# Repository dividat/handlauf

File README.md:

# Handlauf

**PCB Design, Firmware and Driver vor the Dividat Handlauf Extension**

## PCB Design

See the `Handlauf.sch` and `Handlauf.brd` EAGLE files. The CAM output for
production can be found in the `cam.zip` file.

## Firmware

The `Handlauf.ino` is the Arduino based firmware for the built-in Arduino.
Download the "capacitive sensor" and "ewma" library from the Arduino library
manager.

## Driver

The `*.go` files make up the Go based driver for the sensor. It can be built
using the standard Go mechanisms. A compiled version for macOS is available on
the release page: https://github.com/256dpi/handlauf/releases. 

The binary provides the following options:

```
Usage of ./handlauf:
  -addr string
        WebSocket server address (default "0.0.0.0:8080")
  -debug string
        Debug server address e.g. ":1234"
  -freq int
        Sample publish frequency (default 60)
  -min-range float
        The minimum range (default 1000)
  -threshold float
        The threshold for on/off values
```

The driver contains a Web based debug interface to inspect the sensor values.
If the driver is started with the `-debug :1234` flag, the interface is
available at `http://0.0.0.0:1234`.

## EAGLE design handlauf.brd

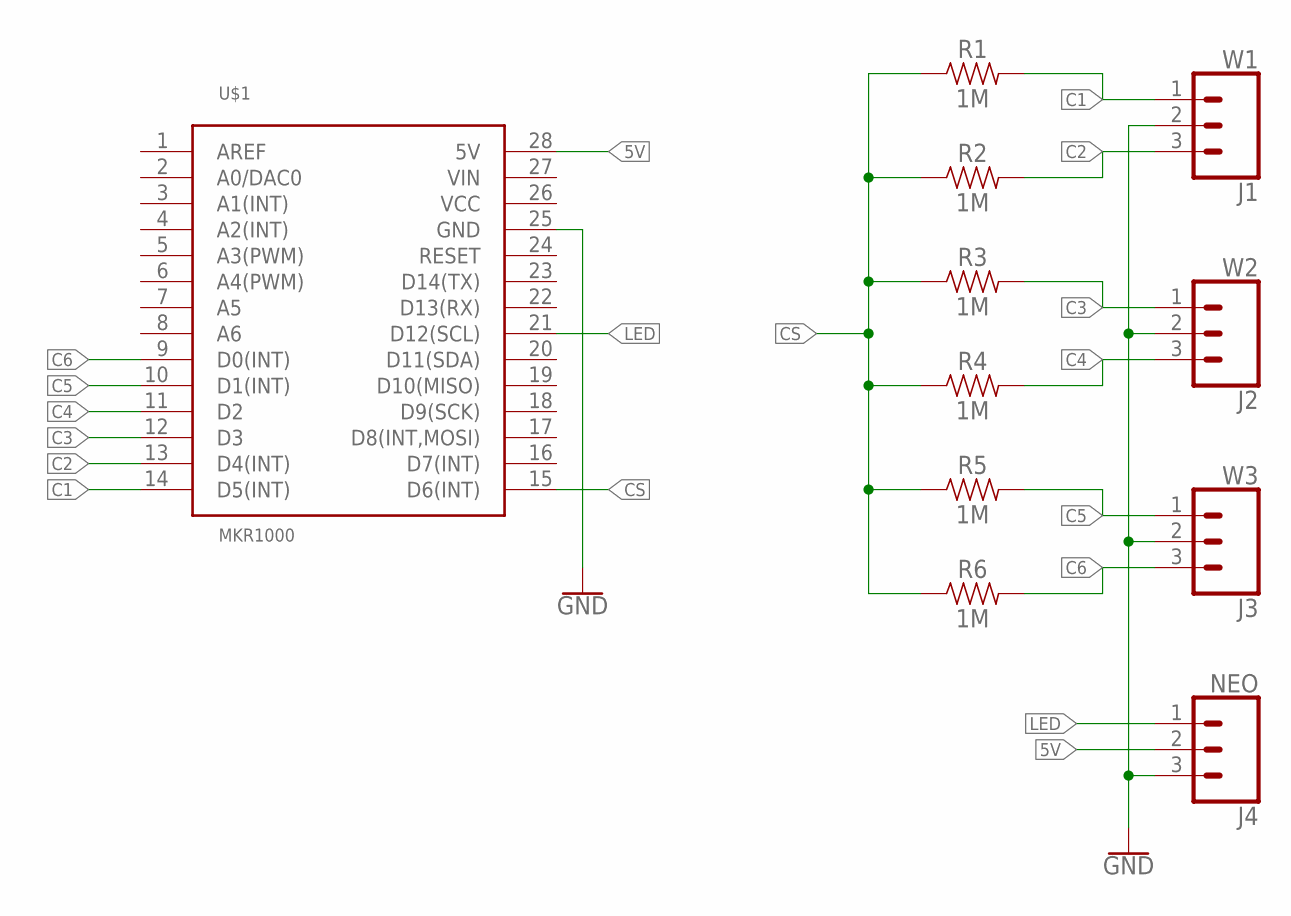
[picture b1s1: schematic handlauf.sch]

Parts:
J1: W1; SCREWTERMINAL-3.5MM-3
J2: W2; SCREWTERMINAL-3.5MM-3
J3: W3; SCREWTERMINAL-3.5MM-3
J4: NEO; 1X03
R1, R2, R3, R4, R5, R6: 1M; AXIAL-0.3
U$1: MKR1000; MKR1000-SOCKET

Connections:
5V: J4.2, U$1.28 (5V)
C1: J1.1, R1.P$2 (2), U$1.14 (D5(INT))
C2: J1.3, R2.P$2 (2), U$1.13 (D4(INT))
C3: J2.1, R3.P$2 (2), U$1.12 (D3)
C4: J2.3, R4.P$2 (2), U$1.11 (D2)
C5: J3.1, R5.P$2 (2), U$1.10 (D1(INT))
C6: J3.3, R6.P$2 (2), U$1.9 (D0(INT))
CS: R1.P$1 (1), R2.P$1 (1), R3.P$1 (1), R4.P$1 (1), R5.P$1 (1), R6.P$1 (1), U$1.15 (D6(INT))
GND: J1.2, J2.2, J3.2, J4.3, U$1.25 (GND)
LED: J4.1, U$1.21 (D12(SCL))

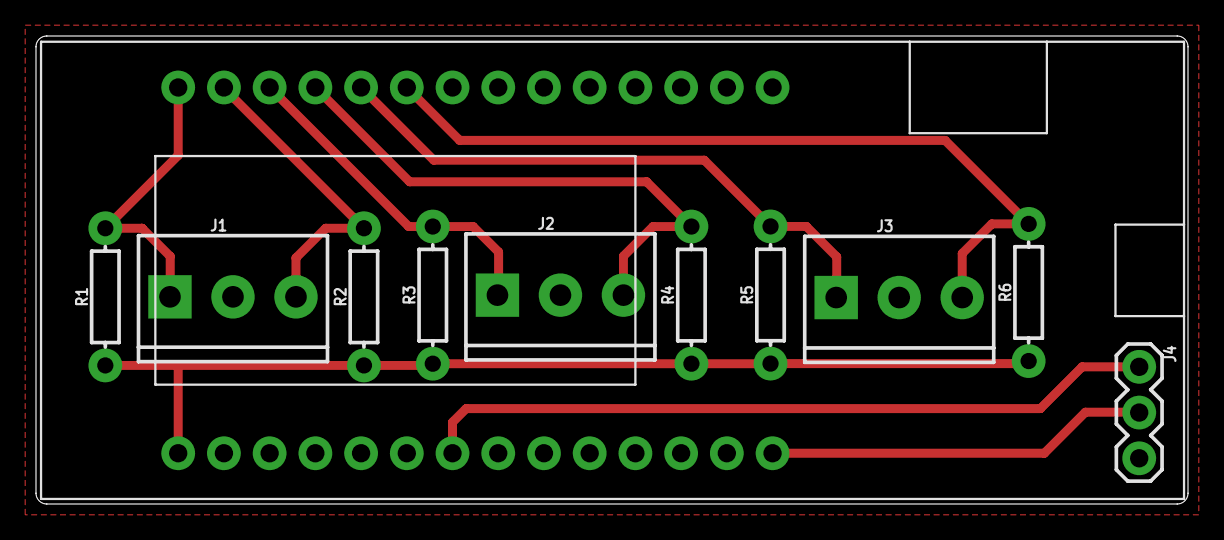
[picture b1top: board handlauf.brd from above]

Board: 2 copper layers, 64.0 x 26.0 mm, 11 parts (0 on the bottom side), 10 nets.

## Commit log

2020-07-21 added firmware
2020-07-21 added pcb
2020-07-21 added basic server
2020-07-21 added adaptive max
2020-07-21 added flags
2020-07-21 added socket.io
2020-07-21 use mqtt
2020-07-21 added basic mqtt connection
2020-07-28 rounded corners
2020-07-29 added cam files
2020-08-18 added basic viz
2020-08-18 added publish frequency
2020-08-18 switched to pure websockets
2020-08-18 small fixes
2020-08-18 support multi lines
2020-08-18 added delay
2020-08-18 added bars
2020-08-18 added god
2020-08-18 trim space
2020-08-24 added multi device support
2020-08-24 cleaned up
2020-08-24 simplified
2020-08-31 added readme
2020-08-31 improved performance
2020-08-31 added histogram based calculation
2020-08-31 added theshold
2020-08-31 added ui
2020-09-08 make usb prefix configurable
2020-09-08 fixed bug
2020-09-08 use custom payload format
2020-09-08 added build script
2020-11-03 updated embed
2021-02-09 Check in vendor/ for nix build

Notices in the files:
parts and their libraries:
SparkFun-Connectors: Licensing: Creative Commons ShareAlike 4.0 International - https://creativecommons.org/licenses/by-sa/4.0
